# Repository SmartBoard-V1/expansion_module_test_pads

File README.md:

# # Expansion Module: Test Pads with LEDs

## Overview
This repository is dedicated to the design and implementation of the Test Pads with LEDs Expansion Module, an advanced diagnostic tool crafted to enhance the testing and debugging processes of electronic circuits. With its integration of 8 test pads linked to LED indicators and an additional LED for power status verification, this module stands as a critical asset for developers. It excels in facilitating the examination of signal integrity within FPGA configurations on SmartBoard connectors, especially useful in identifying potential line damage caused by the integration of improperly designed expansion modules. Moreover, its utility extends to the observation and testing of signal outputs from the FPGA to external analysis equipment, such as oscilloscopes or logic analyzers, making it invaluable for real-time signal monitoring during module communication interface testing.

## Key Features
- **LED Indicators**: Features 8 LEDs associated with test pads for immediate visual feedback on signal status, plus one additional LED to confirm power supply integrity.
- **Dual Functionality**:
  - Enables the testing of signal paths on FPGA pads within SmartBoard connectors, aiding in the quick identification of any damaged lines due to faulty expansion module connections.
  - Facilitates the external monitoring and testing of FPGA output signals, allowing for the rerouting of internal signals to this module for analysis with oscilloscopes or logic analyzers.
- **Versatile Testing Capability**: Specially designed for a broad spectrum of electronic testing and debugging scenarios, enhancing both prototype development and troubleshooting efforts.

## Design Documentation

### Schematic Diagram

*This schematic diagram outlines the layout and connections of the test pads and LEDs, providing a clear guide for replication or modification.*

### Board Design - 2D

*The 2D board design illustrates the placement of LEDs and test pads on the PCB, ensuring optimal accessibility for testing purposes.*

## Contributions and Feedback
We welcome contributions and suggestions for improvements to this module. If you have developed enhancements or have ideas for additional features, please fork the repository, implement your changes, and submit a pull request. For any questions or issues, open an issue in the GitHub repository.

## License
This expansion module is licensed under the MIT License, providing flexibility for both private and commercial use under the following terms:

- **Permission to Use**: Freedom to use, modify, and distribute the module design.
- **Attribution**: While not mandatory, crediting the original author, Adam Łuczak, is appreciated.
- **No Warranty**: Provided "as is", without any warranty; use at your own risk.
- **Liability**: The author bears no liability for any damages or losses.

For full license terms, please refer to the MIT License documentation in this repository.

## Contact
For inquiries or suggestions regarding this project, please contact Adam Łuczak at adam.luczak@outlook.com.

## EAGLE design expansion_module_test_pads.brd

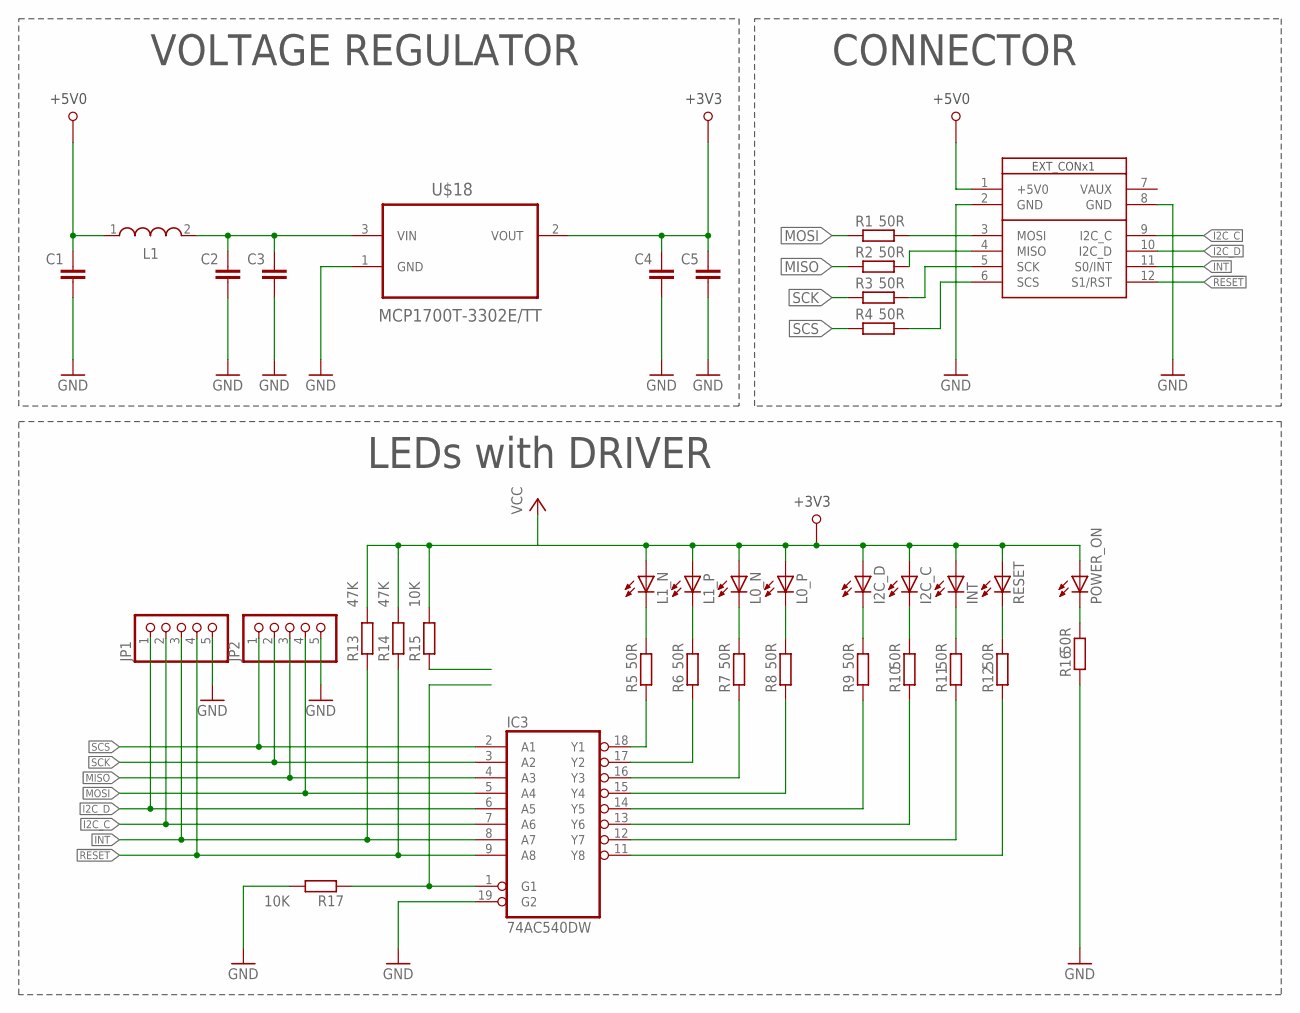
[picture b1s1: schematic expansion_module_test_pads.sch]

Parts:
C1, C2, C3, C4, C5: C-EUC0805; C0805
I2C_C, I2C_D: LEDCHIPLED_0805; CHIPLED_0805
IC3: 74AC540DW; SO20W
INT: LEDCHIPLED_0805; CHIPLED_0805
JP1, JP2: PINHD-1X5; 1X05
L0_N, L0_P, L1_N, L1_P: LEDCHIPLED_0805; CHIPLED_0805
L1: WE-LQ_1210; WE-LQ_M
POWER_ON: LEDCHIPLED_0805; CHIPLED_0805
R1, R2, R3, R4, R5, R6, R7, R8, R9, R10, R11, R12, R16: 50R; R0805
R13, R14: 47K; R0805
R15, R17: 10K; R0805
RESET: LEDCHIPLED_0805; CHIPLED_0805
U$1: SB_EXT_CON_X1_SPI; SB_EXT_CON_X1_FULL
U$18: MCP1700T-3302E/TT; SOT95P237X112-3N

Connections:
!RESET: IC3.9 (A8), JP1.4, R14.1, U$1.12 (S1/RST)
+3V3: C4.2, C5.2, I2C_C.A, I2C_D.A, INT.A, L0_N.A, L0_P.A, L1_N.A, L1_P.A, POWER_ON.A, R13.2, R14.2, R15.2, RESET.A, U$18.2 (VOUT)
+5V0: C1.2, L1.1, U$1.1 (+5V0)
GND: C1.1, C2.1, C3.1, C4.1, C5.1, IC3.10 (GND), IC3.19 (G2), JP1.5, JP2.5, R16.1, R17.2, U$1.2 (GND), U$1.8 (GND), U$18.1 (GND)
I2C_C: IC3.7 (A6), JP1.2, U$1.9 (I2C_C)
I2C_D: IC3.6 (A5), JP1.1, U$1.10 (I2C_D)
INT: IC3.8 (A7), JP1.3, R13.1, U$1.11 (S0/INT)
MISO: IC3.4 (A3), JP2.3, R2.1
MOSI: IC3.5 (A4), JP2.4, R1.1
unnamed: R1.2, U$1.3 (MOSI)
unnamed: R2.2, U$1.4 (MISO)
unnamed: R3.2, U$1.5 (SCK)
unnamed: R4.2, U$1.6 (SCS)
unnamed: IC3.18 (Y1), R5.1
unnamed: IC3.17 (Y2), R6.1
unnamed: IC3.16 (Y3), R7.1
unnamed: C2.2, C3.2, L1.2, U$18.3 (VIN)
unnamed: IC3.15 (Y4), R8.1
unnamed: IC3.14 (Y5), R9.1
unnamed: IC3.13 (Y6), R10.1
unnamed: IC3.12 (Y7), R11.1
unnamed: IC3.11 (Y8), R12.1
unnamed: L1_N.C, R5.2
unnamed: L1_P.C, R6.2
unnamed: L0_N.C, R7.2
unnamed: L0_P.C, R8.2
unnamed: I2C_D.C, R9.2
unnamed: I2C_C.C, R10.2
unnamed: INT.C, R11.2
unnamed: R12.2, RESET.C
unnamed: POWER_ON.C, R16.2
unnamed: IC3.1 (G1), R17.1
SCK: IC3.3 (A2), JP2.2, R3.1
SCS: IC3.2 (A1), JP2.1, R4.1
VCC: IC3.20 (VCC)

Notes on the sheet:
CONNECTOR
VOLTAGE REGULATOR
LEDs with DRIVER

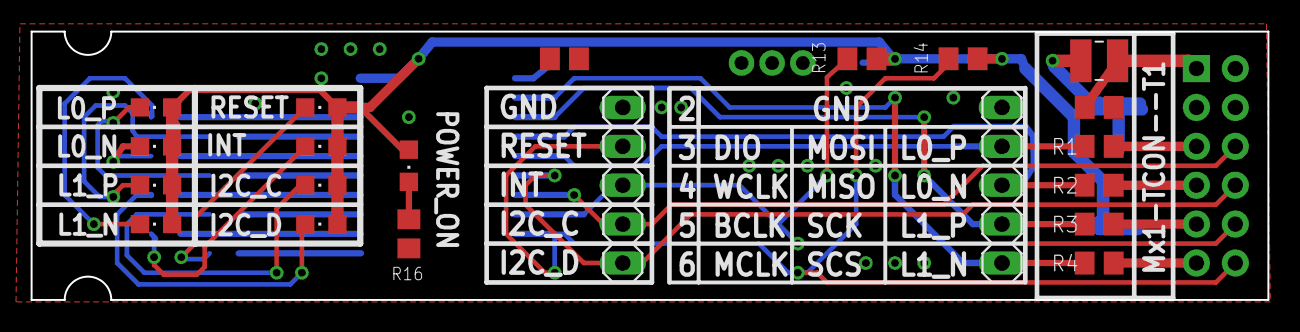
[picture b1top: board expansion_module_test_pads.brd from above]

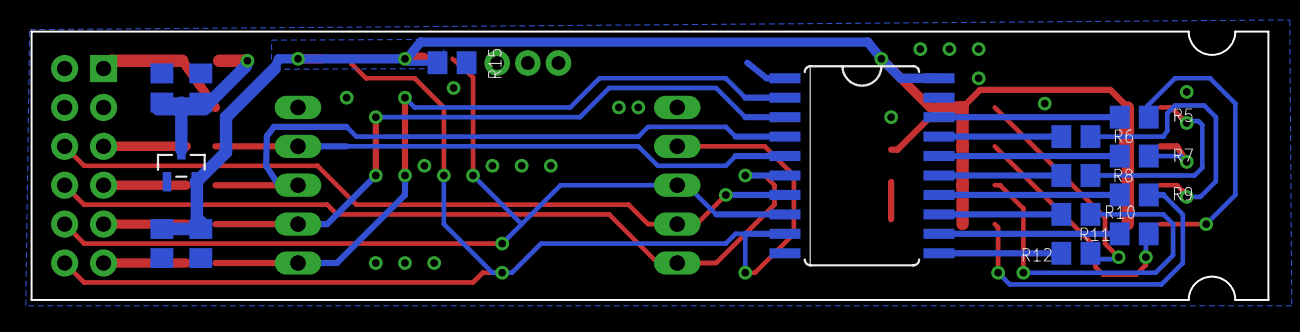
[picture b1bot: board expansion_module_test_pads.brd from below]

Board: 2 copper layers, 80.8 x 17.5 mm, 37 parts (15 on the bottom side), 34 nets.

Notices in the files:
README.md:
License: MIT
parts and their libraries:
EagleLibrary_Wuerth_Elektronik_eiSos_rev: Copyright: Würth Elektronik
